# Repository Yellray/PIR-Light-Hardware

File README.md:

# PIR Triggered Light Module

# Description

This repository contains the electrical schematics, PCB layout, and hardware documentation for a compact passive infrared (PIR) motion-controlled light module with ambient light threshold detection and controlled dimming ramp (fade-in/fade-out).

The system automatically controls lighting based on detected motion and ambient light conditions, ensuring the light only activates in low-light environments. It operates fully in hardware, without requiring software or network connectivity.

The module includes an I/O synchronization port that allows multiple units to be interconnected. When any connected module detects motion, all linked modules are activated simultaneously, enabling coordinated lighting across larger areas such as hallways, staircases, or multiple rooms.

Additionally, the design incorporates a light feedback loop, ensuring motion detection while the controlled light source is active. This prevents the PIR sensor from being shut down by illumination generated by the module itself. Because of this, the light remains continuously on as long as occupancy is detected within the monitored area.

# Schematic

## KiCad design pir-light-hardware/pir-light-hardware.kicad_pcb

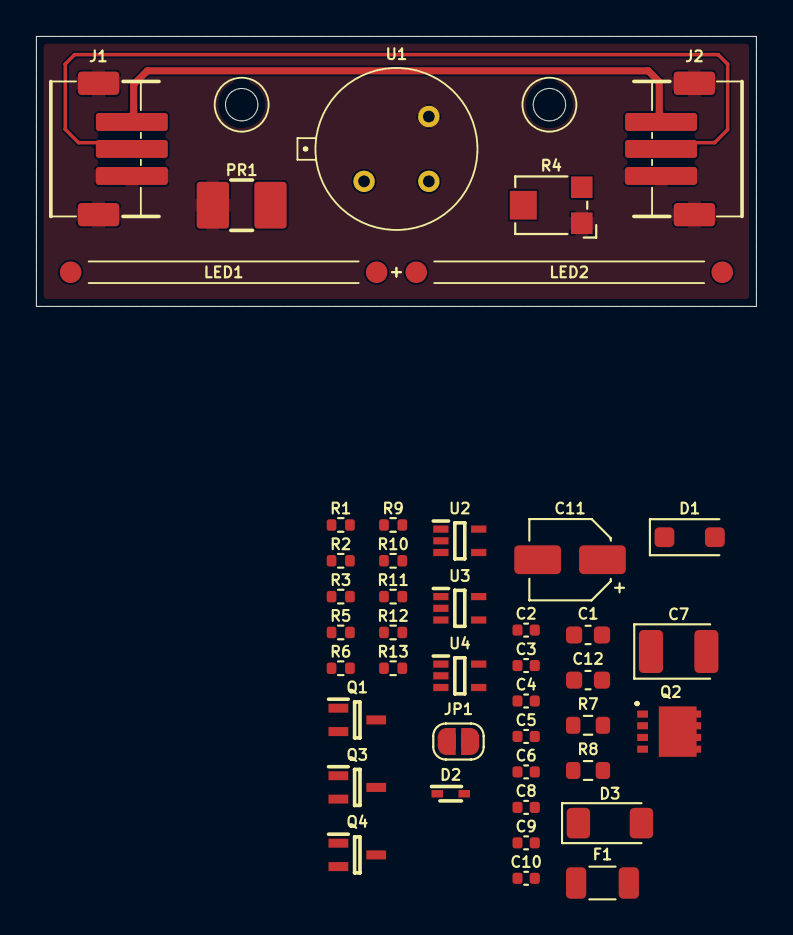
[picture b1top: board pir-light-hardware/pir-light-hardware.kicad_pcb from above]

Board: 2 copper layers, 40.0 x 15.0 mm, 43 parts (0 on the bottom side), 16 nets.

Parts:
C1, C12: 10uF; C_0603_1608Metric
C2, C4, C5, C6, C8, C9, C10: 100nF; C_0402_1005Metric
C3: 10nF; C_0402_1005Metric
C7: 47uF; CP_EIA-3528-12_Kemet-T
C11: 33uF; CP_Elec_4x5.4
D1: 1N5819; D_SOD-123F
D2: 1N5819HWQ-7-F
D3: ZMM5V1; D_MiniMELF
F1: 100mA; R_1206_3216Metric
J1, J2: ZH1.5-3
JP1: Jumper_Open; SolderJumper-2_P1.3mm_Open_RoundedPad1.0x1.5mm
LED1, LED2: LED-ROD
PR1: 8-20kR; GT36528
Q1, Q3: DTA114EUAHE3-TP; SOT65P228X120-3N
Q2: AON7240
Q4: DTC114EUA-TP; SOT65P228X120-3N
R1, R2: 100kR; R_0402_1005Metric
R3, R12, R13: 1MR; R_0402_1005Metric
R4: 200kR; Potentiometer_Bourns_TC33X_Vertical
R5, R9: 10kR; R_0402_1005Metric
R6: R; R_0402_1005Metric
R7, R8: 0R; R_0603_1608Metric
R10: 620kR; R_0402_1005Metric
R11: 47kR; R_0402_1005Metric
U1: AS312; AS312-NEW
U2: M74VHC1GT08DFT2G; SOT65P210X110-5N
U3, U4: LMV331IDCKR; SOT65P210X110-5N

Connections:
3V3: C1.1, C2.1, C7.1, C8.1, C9.1, C10.1, D1.1 (K), F1.2, Q1.2 (GND), R1.1, R2.1, R3.1, R7.1, R8.1, R9.1, U1.1 (VCC), U2.5 (VCC), U3.5 (VCC), U4.5 (VCC)
/ALT: C4.1, R1.2, R4.2, R6.1, U3.3 (-)
/ALV: C5.1, PR1.1, R2.2, U3.1 (+)
/FB: C12.1, JP1.1 (A), Q2.2 (G), R10.2, R13.1, U4.1 (+)
/FBT: C6.1, R3.2, R5.1, U4.3 (-)
/PIR: C3.1, U1.2 (REL), U2.2 (A)
/STL: D2.1 (K), D3.1 (K), J1.2, J2.2, Q4.1 (IN), R11.1
GND: C1.2, C2.2, C3.2, C4.2, C5.2, C6.2, C7.2, C8.2, C9.2, C10.2, C11.2, C12.2, D1.2 (A), D3.2 (A), J1.1, J1.4 (MP), J2.3, J2.4 (MP), JP1.2 (B), PR1.2, Q2.1 (S), Q4.2 (GND), R4.1, R5.2, R6.2, R11.2, R12.2, R13.2, U1.3 (GND), U2.3 (GND), U3.4 (GND), U4.4 (GND)
unnamed: D2.2 (A), U2.4 (Y)
unnamed: LED1.1, R7.2
unnamed: LED2.1, R8.2
unnamed: Q1.1 (IN), Q4.3 (OUT)
unnamed: C11.1, Q1.3 (OUT), R10.1, R12.1
unnamed: LED1.2, LED2.2, Q2.3 (D)
unnamed: Q3.2 (GND), R9.2, U2.1 (B)
VIN: F1.1, J1.3, J2.1

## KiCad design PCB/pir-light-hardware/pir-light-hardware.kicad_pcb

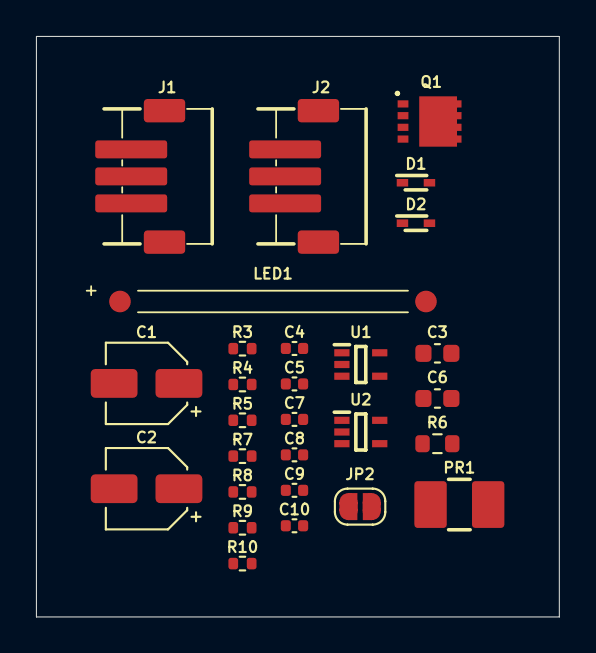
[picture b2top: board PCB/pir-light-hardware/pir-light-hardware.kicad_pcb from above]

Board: 2 copper layers, 29.1 x 32.2 mm, 28 parts (0 on the bottom side), 11 nets, no tracks yet.

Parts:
C1: 33uF; CP_Elec_4x5.4
C2: 47uF; CP_Elec_4x5.4
C3, C6: 10uF; C_0603_1608Metric
C4: 10nF; C_0402_1005Metric
C5, C7, C8, C9, C10: 100nF; C_0402_1005Metric
D1, D2: 1N5819HWQ-7-F
J1, J2: ZH1.5-3
JP2: Jumper_Open; SolderJumper-2_P1.3mm_Open_RoundedPad1.0x1.5mm
LED1: LED-ROD
PR1: 8-20kR; GT36528
Q1: AON7240
R3, R5: 1MR; R_0402_1005Metric
R4: 620kR; R_0402_1005Metric
R6: 0R; R_0603_1608Metric
R7: 100kR; R_0402_1005Metric
R8: 10kR; R_0402_1005Metric
R9, R10: R; R_0402_1005Metric
U1: M74VHC1GT08DFT2G; SOT65P210X110-5N
U2: LMV331IDCKR; SOT65P210X110-5N

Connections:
3V3: C2.1, C5.1, C6.1, C9.1, C10.1, J1.2, J2.2, R6.1, R7.1, R8.1, R9.1, U1.5 (VCC), U2.5 (VCC)
/LLS: C8.1, PR1.1, R7.2, U2.1 (+)
/PIR: C4.1, U1.2 (A)
/REF: C7.1, R9.2, R10.1, U2.3 (-)
GND: C1.2, C2.2, C3.2, C4.2, C5.2, C6.2, C7.2, C8.2, C9.2, C10.2, J1.3, J1.4 (MP), J2.1, J2.4 (MP), JP2.2 (B), PR1.2, Q1.1 (S), R3.2, R5.2, R10.2, U1.3 (GND), U2.4 (GND)
unnamed: D1.2 (A), D2.2 (A_2), U1.4 (Y)
unnamed: C1.1, D1.1 (K), R3.1, R4.1
unnamed: C3.1, JP2.1 (A), Q1.2 (G), R4.2, R5.1
unnamed: LED1.1, R6.2
unnamed: LED1.2, Q1.3 (D)
unnamed: R8.2, U1.1 (B)

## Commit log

2026-06-17 init: create project structure
2026-06-17 chore(kicad): add first part of component libraries
2026-06-17 docs: update readme
2026-06-18 chore(kicad): add next part of component libraries
2026-06-20 chore(kicad): add final part of component libraries
2026-06-20 chore(kicad): add initial electrical schematic
2026-06-20 chore: add power and signal sockets
2026-06-20 feat: add shared trigger functionality
2026-06-20 chore: add protection components
2026-06-22 feat: sustain motion detection while own light is active
2026-06-22 docs: add schematic image to README
2026-06-22 docs: crop title block from schematic snapshot
2026-06-22 style: tweak schematic visuals
2026-06-22 style: add notes to schematic
2026-06-23 chore: rework sustain feature, add actual components to schematic
2026-06-23 docs: update readme content
2026-06-23 chore: mark general PCB dimensions
2026-06-24 docs: add top pcb snapshot
2026-06-24 chore: add top pcb layout
2026-06-24 style: add dimension values of pcb
